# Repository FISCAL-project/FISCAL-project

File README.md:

# FISCAL-project
FISCAL, that means Fine Instrument String Calibration by ADA Lab, is a project that intends to help musicians to fine tune instruments.

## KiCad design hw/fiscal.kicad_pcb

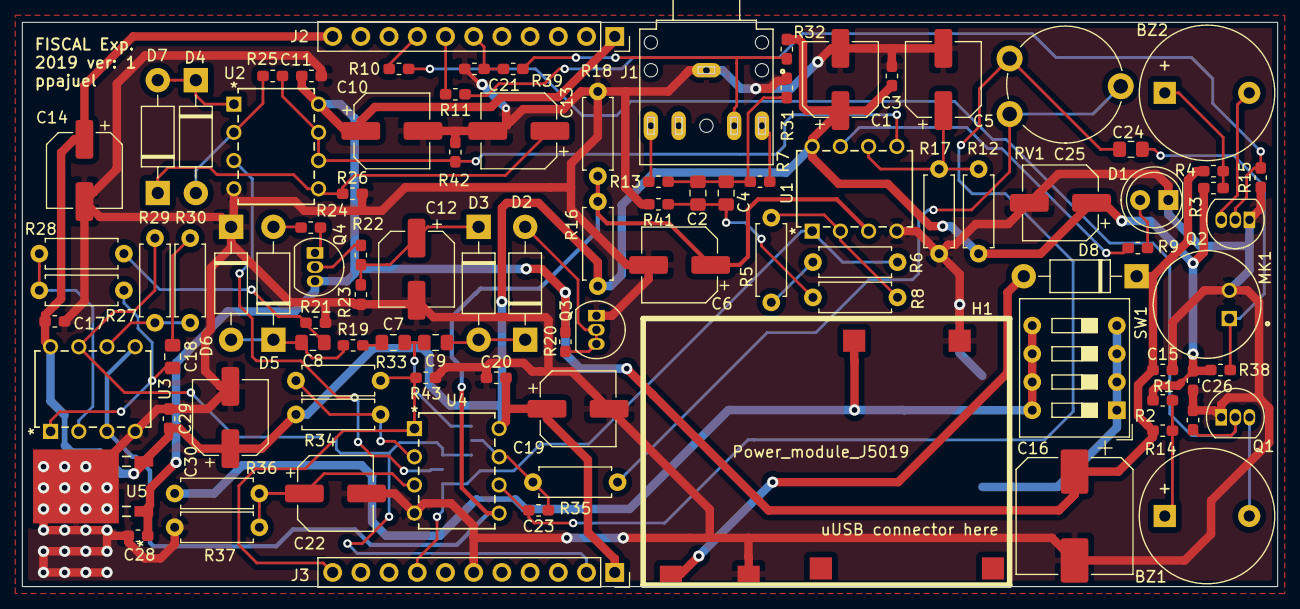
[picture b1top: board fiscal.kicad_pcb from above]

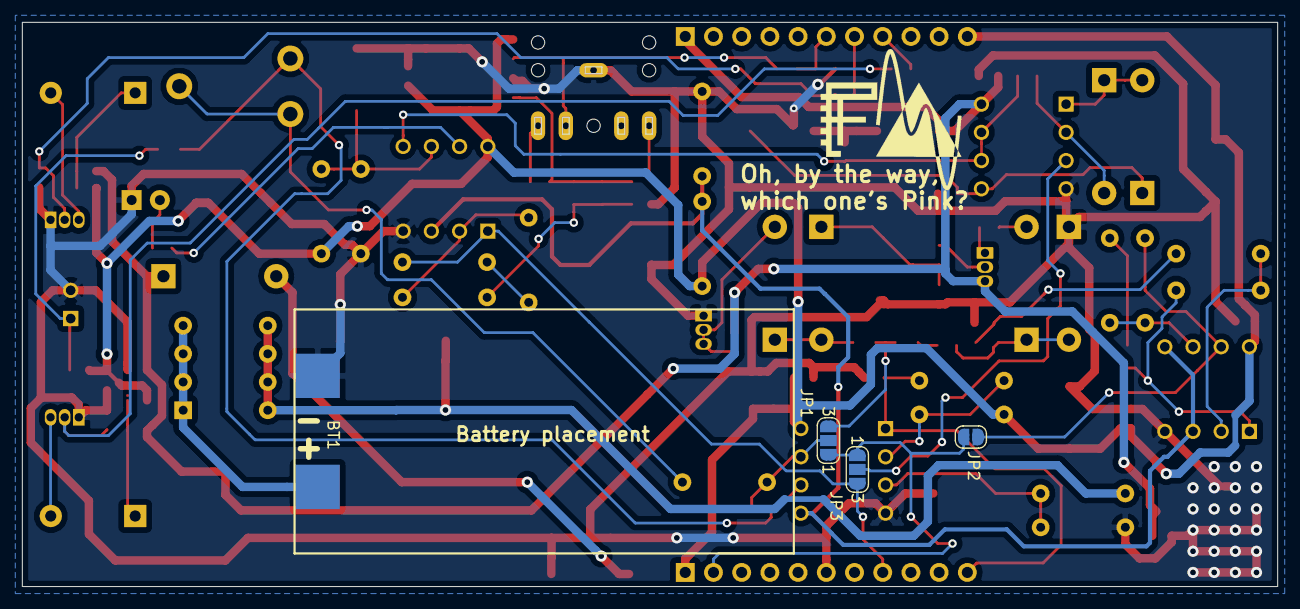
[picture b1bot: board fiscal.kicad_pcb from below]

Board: 2 copper layers, 113.0 x 50.7 mm, 101 parts (4 on the bottom side), 55 nets.

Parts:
BT1: 3V7@450mAh; 1-LIPO-400
BZ1, BZ2: Buzzer; Buzzer_12x9.5RM7.6
C1, C5, C6, C10, C12, C13, C14, C19, C22, C25, C30: 22u; CP_Elec_6.3x5.9
C2, C4, C7, C8, C9, C18, C24: 47u; C_0805_2012Metric_Pad1.15x1.40mm_HandSolder
C3, C11, C15, C17, C20, C21, C26, C28, C29: 100n; C_0603_1608Metric_Pad1.05x0.95mm_HandSolder
C16: 470u; CP_Elec_10x10
C23: 10p; C_0603_1608Metric_Pad1.05x0.95mm_HandSolder
D1: RED TH; LED_D5.0mm
D2, D3, D5, D6, D8: SB160; D_DO-41_SOD81_P10.16mm_Horizontal
D4, D7: 1N4004; D_DO-41_SOD81_P10.16mm_Horizontal
H1: Power_module_J5019; J5019
J1: 35RAPC4BHN2
J2: P1_evens; PinSocket_1x11_P2.54mm_Vertical
J3: P2_odds; PinSocket_1x11_P2.54mm_Vertical
JP1, JP3: SolderJumper_3_Open; SolderJumper-3_P1.3mm_Open_RoundedPad1.0x1.5mm_NumberLabels
JP2: SolderJumper_2_Open; SolderJumper-2_P1.3mm_Open_RoundedPad1.0x1.5mm
MK1: CME7
Q1, Q2, Q3, Q4: 2N3904; TO-92_Inline
R1, R2, R3, R4: 0R; R_0603_1608Metric_Pad1.05x0.95mm_HandSolder
R5, R8, R17, R33, R35, R37: 22K; R_Axial_DIN0207_L6.3mm_D2.5mm_P7.62mm_Horizontal
R6, R27, R29: 47K; R_Axial_DIN0207_L6.3mm_D2.5mm_P7.62mm_Horizontal
R7, R13: 33R; R_0603_1608Metric_Pad1.05x0.95mm_HandSolder
R9: 220R; R_0603_1608Metric_Pad1.05x0.95mm_HandSolder
R10, R11, R19, R20, R31: 10K; R_0603_1608Metric_Pad1.05x0.95mm_HandSolder
R12: 4K7; R_Axial_DIN0207_L6.3mm_D2.5mm_P7.62mm_Horizontal
R14, R15, R25: 22K; R_0603_1608Metric_Pad1.05x0.95mm_HandSolder
R16, R18, R28, R30, R34, R36: 10K; R_Axial_DIN0207_L6.3mm_D2.5mm_P7.62mm_Horizontal
R21, R23, R32, R41, R42, R43: 100K; R_0603_1608Metric_Pad1.05x0.95mm_HandSolder
R22: 100R; R_0603_1608Metric_Pad1.05x0.95mm_HandSolder
R24: 4K7; R_0603_1608Metric_Pad1.05x0.95mm_HandSolder
R26: 1Meg; R_0603_1608Metric_Pad1.05x0.95mm_HandSolder
R38: 2K2; R_0603_1608Metric_Pad1.05x0.95mm_HandSolder
R39: 47K; R_0603_1608Metric_Pad1.05x0.95mm_HandSolder
RV1: 100K; Potentiometer_Piher_PT-10-V10_Vertical
SW1: SW_DIP_x04; SW_DIP_SPSTx04_Slide_9.78x12.34mm_W7.62mm_P2.54mm
U1, U2, U3, U4: 8-PDIP
U5: LF33ABDT

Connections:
+3V3: C1.1, C3.2, C14.1, C17.2, C19.1, C20.2, C25.1, C26.1, C29.1, C30.1, J2.11, J3.1, R1.2, R3.1, R12.1, R16.2, R32.2, R34.2, R38.1, U1.8, U3.8, U4.8, U5.2
+5V: C10.1, C11.2, C15.1, C16.1, C28.1, D8.1, J2.1, Q4.3, R2.1, R4.1, R20.1, U2.8, U5.1
/AVC_AMP_stg1_out: C18.1, R27.1, U3.1
/Fdbck_ppp: D4.2, R25.2, U2.2
/JS: J1.11, R32.1, R39.2
GNDD: BT1.2, C1.2, C3.1, C5.2, C6.2, C10.2, C11.1, C12.2, C13.2, C14.2, C15.2, C16.2, C17.1, C19.2, C20.1, C21.1, C22.2, C25.2, C26.2, C28.2, C29.2, C30.2, D1.1, D6.1, H1.4, H1.5, J1.1, J3.6, MK1.2, Q1.1, Q2.1, Q3.1, R14.1, R15.1, R17.2, R18.2, R21.2, R23.2, R26.2, R31.2, R37.2, R41.2, R42.2, R43.1, U1.4, U2.4, U3.4, U4.4, U5.3
Mic_in_AVC_out: C8.1, R21.1, R28.2
Mic_in_analog: C23.1, JP1.2, R35.2, U4.7
unnamed: BT1.1, SW1.1, SW1.2, SW1.3, SW1.4
unnamed: BZ1.1, R1.1, R2.2
unnamed: BZ1.2, Q1.3
unnamed: BZ2.1, R3.2, R4.2
unnamed: BZ2.2, Q2.3
unnamed: C2.1, C4.1, R8.2, R41.1
unnamed: C2.2, C4.2, R7.1, R13.1, R31.1
unnamed: C5.1, R12.2, R17.1, U1.6
unnamed: C7.1, R19.2
unnamed: C7.2, C9.2, JP1.3
unnamed: C8.2, D5.1, D6.2, R19.1
unnamed: C9.1, D2.1, D3.2
unnamed: C12.1, D3.1, R22.2, R23.1
unnamed: C13.1, D7.1, R26.1, U2.5
unnamed: C18.2, R30.1
unnamed: C22.1, R36.1, R37.1, U4.3
unnamed: C23.2, C24.2, RV1.3, U4.6
unnamed: C24.1, MK1.1, R38.2
unnamed: D1.2, R9.1
unnamed: D2.2, Q3.2, Q3.3, R20.2
unnamed: D4.1, D7.2, U2.1
unnamed: D5.2, R24.1
unnamed: D8.2, H1.6
unnamed: J1.2, R13.2
unnamed: J1.3, R7.2
unnamed: JP2.1, R29.2, U3.7
unnamed: JP3.2, U2.3
unnamed: Q1.2, R10.1, R14.2
unnamed: Q2.2, R11.1, R15.2
unnamed: Q4.1, R24.2
unnamed: Q4.2, R22.1
unnamed: R5.1, R6.2
unnamed: R5.2, R8.1, U1.2
unnamed: R9.2, U1.7
unnamed: R27.2, R28.1, U3.2
unnamed: R29.1, R30.2, U3.6
unnamed: R33.2, R34.1, U4.2
unnamed: R35.1, RV1.1, RV1.2
PA5_VBAT: J3.11, R33.1, R43.2, U4.1
PC3_LSin: J3.8, JP3.3, R6.1, U1.1
PC13_Jacksense: C21.2, J2.6, R39.1
PE3_Buzzer2: J2.8, R10.2
PE5_Buzzer1: J2.7, R11.2
PF6_MICin: J3.2, JP1.1, JP2.2, JP3.1
Peak_output: R25.1, R42.1, U1.5, U2.6, U2.7
VBAT: H1.3, R36.2, SW1.5, SW1.6, SW1.7, SW1.8
VGND: C6.1, R16.1, R18.1, U1.3, U3.3, U3.5, U4.5

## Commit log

2018-12-10 add obj directories in .gitignore
2018-12-16 Initial hardware folder commit
    This commit also contains the general design of the hardware
2018-12-16 hw: daily release
2019-01-13 doc/sim: AVC spice simulations and results with 1N34A diode
2019-08-26 Added AVC workbook simulations and more results
2019-08-26 Added software (sw) and mechanical (mec) directories
2019-08-27 Fixed absolute paths
2019-08-27 Added main logo
2019-09-11 hw: res and cap footprint optimizations
2019-09-11 hw: starting to place components in layout
2019-09-14 hw: added layout optimizations
    -> simplified the number of voltage dividers
    -> change lipo footprint
2019-09-15 hw: daily release
    starting to route layout
2019-09-17 doc: avc: added more diode candidates for AVC
2019-09-17 hw: daily release
    Added jacksense functionality
2019-09-22 hw: added layout DGND copper pours
2019-09-22 hw: added gerbers
2019-10-12 sim: added more simulations and libraries
2019-10-12 hw: minor modifications
2019-10-12 hw: added bill of materials
    Also fixed an absolute path on AVC.sch
2019-10-29 hw: minor avc resistor value modification
    R21: 22K -> 100K
2020-02-22 hw: fix minijack sense

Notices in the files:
hw/fiscal.kicad_pcb:
GNU GENERAL PUBLIC LICENSE Version 3
